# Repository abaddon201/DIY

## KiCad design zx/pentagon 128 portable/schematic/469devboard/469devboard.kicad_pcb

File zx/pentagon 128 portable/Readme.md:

# Tasks
1. build devboard for stm32f469II
2. build devboard for rom/ram
3. build devboard for Z80
3. create tap player
4. build prototype
5. create vg93 emulation
6. add AY

# Thougths
1. Use PF register for address line (placed on two neightbour sides)
2. PG0-PG7 - data pins (PI8 - slow, PI2 - absent)

2. Use PI4-11 for data line (also)

Don't use PA4, PA5 for +5V
PI8 - sow port
PC13, PC14, PC15 - slow ports (2 MHz max)

# Hardware

## Description

Cone is built from "original" Z80 CPU. Rom is extended to 128K and it's EEPROM, this can help to program it from the 
STM32 microcontroller. RAM changed to the SRAM, it's a 128K parallel RAM chip (possibly I'll extend it, but nor sure).
Music soprocessor is a AY3-8910/8912 successor: YM2149F.
All other parts would be replaced by STM32 microcontroller.
STM32 would emulate VG93 (Floppy drive), Tape playing, and create real image on the screen. It's also would
work as RAM/ROM page selector and would provide tact frequency for the CPU and AY. Also it would generate INT signal
to the CPU.

## Known issues

1.  STM32 is a 3.3V chip, but it has +5V tolerant inputs. Also all other selected chips are
TTL compatible, except Z80 CPU. Current approach to solve this: use signal converters for all input/output signals
for Z80. But it adds atleast 4 chips such that.
2. Joystick selector: I want to map different layouts to the joystic (Interface 2, QAOP_Space, Cursor, Kempston).
Possibly I can use a https://www.chipdip.ru/product/sn74ls125ad chip for that...

## Parts

STM32F469IIT6 - soldered by jlcpcb (too many small pins)
GLS29EE010-70-4C-NHE - ROM https://ru.mouser.com/ProductDetail/Greenliant/GLS29EE010-70-4C-NHE?qs=bAdOcXfFoy0toSXpScwIgg%3D%3D
IS62C1024AL-35QLI - RAM https://ru.mouser.com/ProductDetail/ISSI/IS62C1024AL-35QLI?qs=tFgq3%2FJV4HjpRgQnMjsF2Q%3D%3D
Screen - FSMC module with touchscreen http://www.lcdwiki.com/3.2inch_16BIT_Module_ILI9341_SKU:MRB3205
crystal - 8MHz https://ru.mouser.com/ProductDetail/815-ABM3B8MHZ101UT
tantalum capacitors - https://ru.mouser.com/ProductDetail/581-TPSB225K025R1200
miniUSB - https://ru.mouser.com/ProductDetail/Amphenol-FCI/10033526-N3212LF?qs=LmzVcvYPptRTPTxae6JWyQ%3D%3D
TXB0108 - level converter - https://www.ti.com/lit/ds/symlink/txb0108.pdf?HQS=TI-null-null-mousermode-df-pf-null-wwe&ts=1600075026418&ref_url=https%253A%252F%252Fru.mouser.com%252F

# Notes

## ZX Keyboard layout

https://d2j6dbq0eux0bg.cloudfront.net/images/9970794/532242200.jpg

## ZX memory layout

Memory selector port:
0x7ffd

D0-D2 - page number at 0xC000-0xFFFF
D3 - 0 - regular screen, 1 - extended (0xC000-)
D4 - 0 - 128K ROM, 1 - 48K ROM
D5 - port lock
D6-D7 - unused

Pages layouted as:

| | | | |
| 0xFFFF | | | |
| |    CPU3 | RAM0 | A14=1,A15=1 |
| 0xC000 | | | |
| 0xBFFF | | | |
| | CPU2 | RAM2 | A14=0, A15=1 |
| 0x8000 | | | |
| 0x7FFF | | | |
| | CPU1 | RAM5 | A14=1, A15=0 |
| 0x4000 | | | |
| 0x3FFF | | | |
| | CPU0 | ROM0 | A14=0, A15=0 |
| 0x0000 | | | |

http://zxbyte.ru/speccybob.htm

## INT

Freq 50Hz
Period: 20ms
Positive: 100 us
Negative: 19.9 ms

## Tape

### Sound gen

Calculation of the timer:

Arr = Fclk/(Nsamples*Fsound) - 1

### Format

Pilot tone: 807 Hz 2sec for data block, 5 sec for the header
Sync impulse: 667 tacts up, 735 tacts down
1: 1710 tacts up, down (2047 Hz)
0: 855 tacts up, down (1023 Hz)
http://zx-info.ru/?rc=12&id=5

## Screen

### Colors table

https://en.m.wikipedia.org/wiki/ZX_Spectrum_graphic_modes

## VG93

https://zx-pk.ru/threads/30269-emulyator-kontrollera-diskovoda-beta-disk-na-avr.html

## Schemes

https://zx-pk.ru/threads/940-scorpion-zs-256-turbo-(skhema).html
https://zx-pk.ru/threads/27819-pentagon-128k-opisanie-naladki.html
https://zx-pk.ru/threads/23343-novaya-plata-pentagon-128k-modifikatsiya-2014-g.html
https://m.habr.com/ru/post/498222/
http://zxdn.narod.ru/hardware.htm
http://micklab.ru/ZX%20Spectrum/Pentagon128.htm
https://www.cxemateka.ru/en/building_zx_spectrum_128k_clone_beta_disk_interface_ay_3_8910_ym2149f/all
https://zx-pk.ru/threads/27819-pentagon-128k-opisanie-naladki.html
https://zx-pk.ru/threads/23343-novaya-plata-pentagon-128k-modifikatsiya-2014-g.html
http://sblive.narod.ru/ZX-Spectrum/Pentagon128k/Pentagon128k.htm

## File formats

http://speccy.info/SCL
https://github.com/shred/tzxtools/tree/master/docs
http://www.seasip.info/ZX/unix.html

# Links

AY https://bulba.untergrund.net/elect.htm

https://documentation.help/BASin/format_tape.html
https://trolsoft.ru/ru/sch/zx-tapper
http://arduitape.blogspot.com/2016/10/introducing-tzxduino.html?m=1
https://m.habr.com/ru/post/330752/
http://zx-info.ru/?rc=12&id=5

Doing power lines right:
https://www.youtube.com/watch?v=klHu-08zyhw&list=PLiu4O2eIDAdURfQ2yeAJLD7160RrJCH3i&index=4

Ben Heck's pzx v2: https://github.com/thebenheckshow/204-tbhs-zx-kit
chips analogues: https://cxem.net/sprav/sprav48.php
zx hardware articles: https://zxpress.ru/menu/1/193
zx extended memory (128K) 
https://zxpress.ru/article.php?id=9971
http://speccy.info/%D0%9F%D0%BE%D1%80%D1%82_7FFD

pentagon timings: 
http://hype.retroscene.org/blog/773.html
https://zx-pk.ru/threads/21212-tajmingi-pentagon-128-).html?p=598258&viewfull=1#post598258

zx tr-dos: http://zxpress.ru/book_articles.php?id=1868

zx ULA verilog: 
https://github.com/fabriziotappero/ip-cores/tree/video_controller_ula_chip_for_zx_spectrum
https://opencores.org/projects/zx_ula

NedoPc:
http://nedopc.com/zxevo/zxevo.php

emulators: https://www.emu-land.net/computers/zx_spectrum/emuls/windows
zx rom disassembly: https://www.esocop.org/docs/CompleteSpectrumROMDisassemblyThe.pdf

# Datasheets

Z80 http://www.farnell.com/datasheets/91822.pdf?_ga=2.86094616.1077264973.1600187324-1828024949.1597676628
DataSheet https://ru.mouser.com/datasheet/2/176/71061-1102136.pdf
crystal https://ru.mouser.com/datasheet/2/3/abm3b-1774998.pdf
ferrite bead https://ru.mouser.com/datasheet/2/281/ENFA0003-1879738.pdf

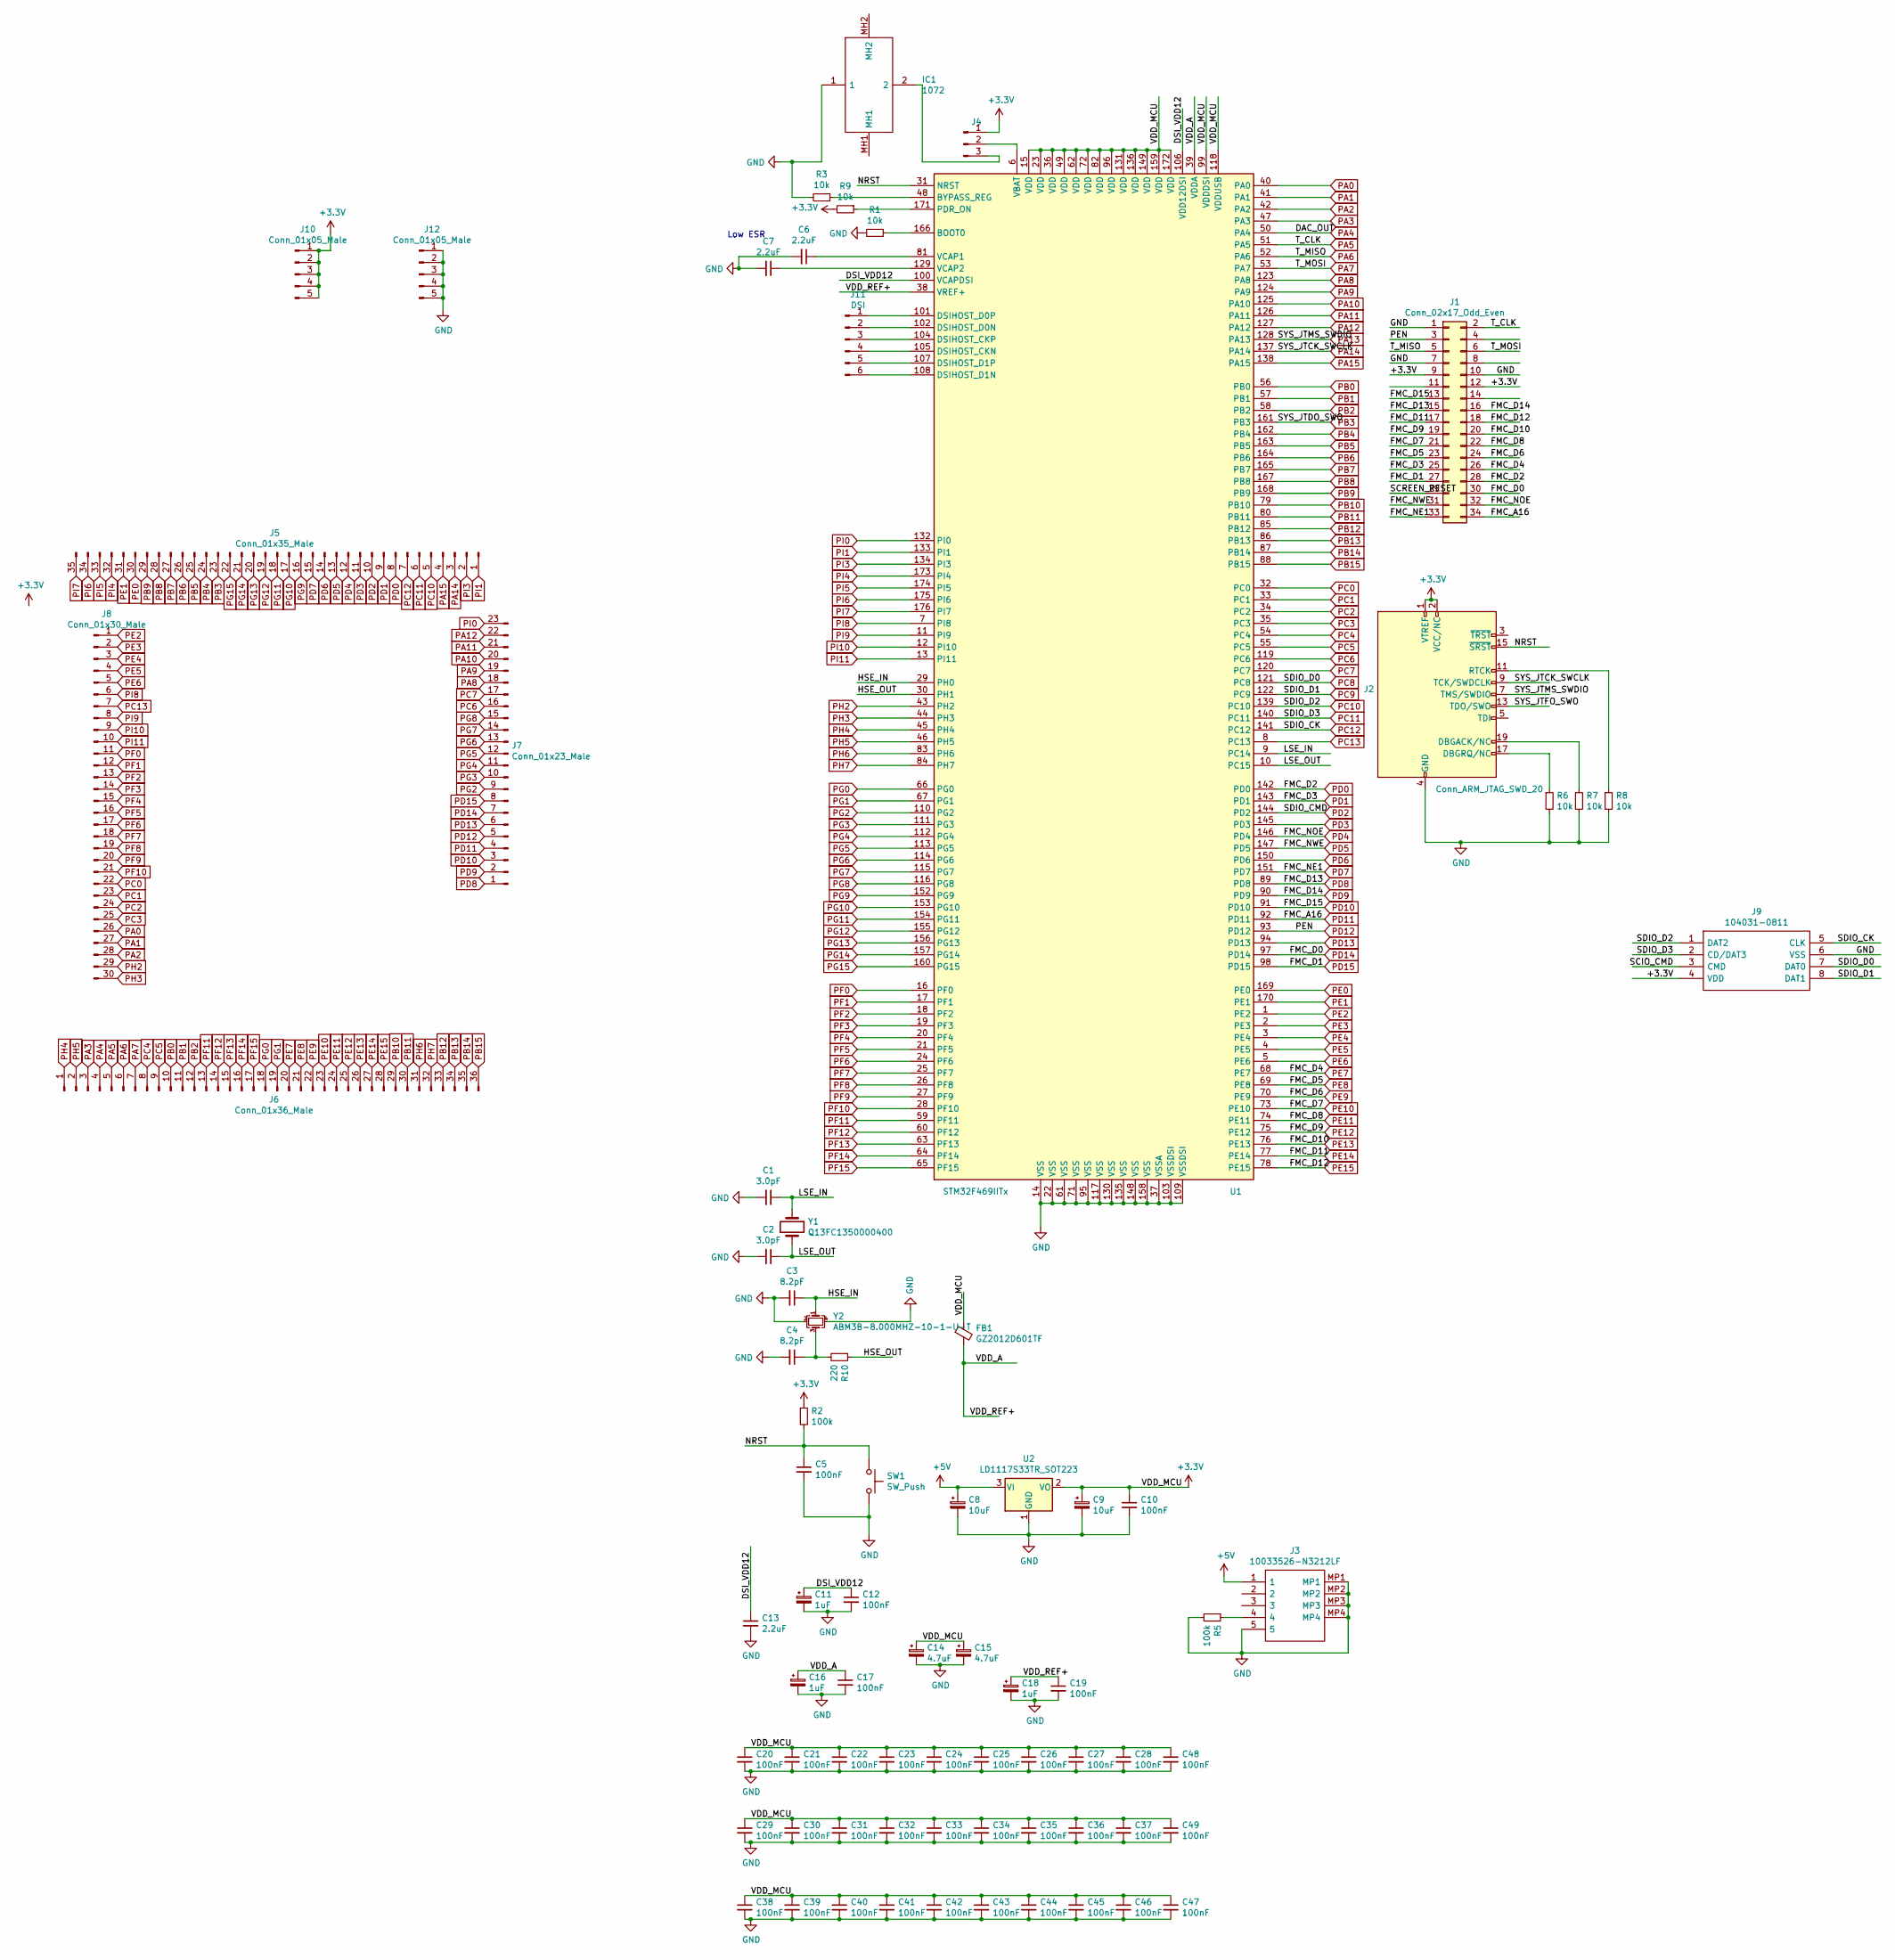
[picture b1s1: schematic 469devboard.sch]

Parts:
C1, C2: 3.0pF; C_0402_1005Metric
C3, C4: 8.2pF; C_0402_1005Metric
C5, C10, C12, C17, C19, C20, C21, C22, C23, C24, C25, C26, C27, C28, C29, C30, C31, C32, C33, C34, C35, C36, C37, C38, C39, C40, C41, C42, C43, C44, C45, C46, C47, C48, C49: 100nF; C_0402_1005Metric
C6, C7: 2.2uF; C_1210_3225Metric_Pad1.42x2.65mm_HandSolder
C8, C9: 10uF; C_0402_1005Metric
C11, C16, C18: 1uF; C_0402_1005Metric
C13: 2.2uF; C_0402_1005Metric
C14, C15: 4.7uF; C_0402_1005Metric
FB1: GZ2012D601TF; C_0805_2012Metric
IC1: 1072; Mouser Part Number 534-1072
J1: Conn_02x17_Odd_Even; PinSocket_2x17_P2.54mm_Vertical
J2: Conn_ARM_JTAG_SWD_20; PinHeader_2x10_P2.54mm_Vertical
J3: 10033526-N3212LF; 10033526N3212LF; Mouser Part Number 649-10033526-N3212LF
J4: Conn_01x03_Male; PinHeader_1x03_P2.54mm_Vertical
J5: Conn_01x35_Male; PinHeader_1x35_P2.54mm_Vertical
J6: Conn_01x36_Male; PinHeader_1x36_P2.54mm_Vertical
J7: Conn_01x23_Male; PinHeader_1x23_P2.54mm_Vertical
J8: Conn_01x30_Male; PinHeader_1x30_P2.54mm_Vertical
J9: 104031-0811; 1040310811; Mouser Part Number 538-104031-0811
J10, J12: Conn_01x05_Male; PinHeader_1x05_P2.54mm_Vertical
J11: DSI; PinHeader_1x06_P2.54mm_Vertical
R1, R3, R6, R7, R8, R9: 10k; R_0402_1005Metric
R2, R5: 100k; R_0402_1005Metric
R10: 220; R_0402_1005Metric
SW1: SW_Push; SW_DIP_SPSTx01_Slide_6.7x4.1mm_W6.73mm_P2.54mm_LowProfile_J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
U1: STM32F469IITx; LQFP-176_24x24mm_P0.5mm
U2: LD1117S33TR_SOT223; SOT-223-3_TabPin2
Y1: Q13FC1350000400; Crystal_SMD_G8-2Pin_3.2x1.5mm
Y2: ABM3B-8.000MHZ-10-1-U-T; Crystal_SMD_Abracon_ABM3B-4Pin_5.0x3.2mm

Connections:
+3V3: C9.1, C10.1, C14.1, C15.1, C20.1, C21.1, C22.1, C23.1, C24.1, C25.1, C26.1, C27.1, C28.1, C29.1, C30.1, C31.1, C32.1, C33.1, C34.1, C35.1, C36.1, C37.1, C38.1, C39.1, C40.1, C41.1, C42.1, C43.1, C44.1, C45.1, C46.1, C47.1, C48.1, C49.1, FB1.1, J2.1 (VTREF), J2.2 (VCC/NC), J4.1, J10.1, J10.2, J10.3, J10.4, J10.5, R2.1, R9.2, U1.15 (VDD), U1.23 (VDD), U1.36 (VDD), U1.49 (VDD), U1.62 (VDD), U1.72 (VDD), U1.82 (VDD), U1.96 (VDD), U1.99 (VDDDSI), U1.118 (VDDUSB), U1.131 (VDD), U1.136 (VDD), U1.149 (VDD), U1.159 (VDD), U1.172 (VDD), U2.2 (VO)
+5V: C8.1, J3.1, U2.3 (VI)
/+3.3V: J1.9, J1.12, J9.4 (VDD)
/DSI_VDD12: C11.1, C12.1, C13.1, U1.100 (VCAPDSI), U1.106 (VDD12DSI)
/HSE_IN: C3.1, U1.29 (PH0), Y2.1
/HSE_OUT: R10.1, U1.30 (PH1)
/LSE_IN: C1.1, U1.9 (PC14), Y1.1
/LSE_OUT: C2.1, U1.10 (PC15), Y1.2
/NRST: C5.1, J2.15 (~SRST~), R2.2, SW1.1, U1.31 (NRST)
/VDD_A: C16.1, C17.1, C18.1, C19.1, FB1.2, U1.38 (VREF+), U1.39 (VDDA)
GND: C1.2, C2.2, C3.2, C4.2, C5.2, C6.2, C7.2, C8.2, C9.2, C10.2, C11.2, C12.2, C13.2, C14.2, C15.2, C16.2, C17.2, C18.2, C19.2, C20.2, C21.2, C22.2, C23.2, C24.2, C25.2, C26.2, C27.2, C28.2, C29.2, C30.2, C31.2, C32.2, C33.2, C34.2, C35.2, C36.2, C37.2, C38.2, C39.2, C40.2, C41.2, C42.2, C43.2, C44.2, C45.2, C46.2, C47.2, C48.2, C49.2, IC1.1, J1.1, J1.7, J1.10, J2.4 (GND), J2.6 (GND), J2.8 (GND), J2.10 (GND), J2.12 (GND), J2.14 (GND), J2.16 (GND), J2.18 (GND), J2.20 (GND), J3.5, J3.MP1, J3.MP2, J3.MP3, J3.MP4, J9.6 (VSS), J12.1, J12.2, J12.3, J12.4, J12.5, R1.2, R3.2, R5.2, R6.2, R7.2, R8.2, SW1.2, U1.14 (VSS), U1.22 (VSS), U1.37 (VSSA), U1.61 (VSS), U1.71 (VSS), U1.95 (VSS), U1.103 (VSSDSI), U1.109 (VSSDSI), U1.117 (VSS), U1.130 (VSS), U1.135 (VSS), U1.148 (VSS), U1.158 (VSS), U2.1 (GND), Y2.2, Y2.4
unnamed: C4.1, R10.2, Y2.3
unnamed: C6.1, U1.81 (VCAP1)
unnamed: C7.1, U1.129 (VCAP2)
unnamed: IC1.2, J4.3
unnamed: J2.11 (RTCK), R8.1
unnamed: J2.17 (DBGRQ/NC), R6.1
unnamed: J2.19 (DBGACK/NC), R7.1
unnamed: J3.4, R5.1
unnamed: J4.2, U1.6 (VBAT)
unnamed: J11.1, U1.101 (DSIHOST_D0P)
unnamed: J11.2, U1.102 (DSIHOST_D0N)
unnamed: J11.3, U1.104 (DSIHOST_CKP)
unnamed: J11.4, U1.105 (DSIHOST_CKN)
unnamed: J11.5, U1.107 (DSIHOST_D1P)
unnamed: J11.6, U1.108 (DSIHOST_D1N)
unnamed: R1.1, U1.166 (BOOT0)
unnamed: R3.1, U1.48 (BYPASS_REG)
unnamed: R9.1, U1.171 (PDR_ON)
PA0: J8.26, U1.40 (PA0)
PA1: J8.27, U1.41 (PA1)
PA2: J8.28, U1.42 (PA2)
PA3: J6.3, U1.47 (PA3)
PA4: J6.4, U1.50 (PA4)
PA5: J1.2, J6.5, U1.51 (PA5)
PA6: J1.5, J6.6, U1.52 (PA6)
PA7: J1.6, J6.7, U1.53 (PA7)
PA8: J7.18, U1.123 (PA8)
PA9: J7.19, U1.124 (PA9)
PA10: J7.20, U1.125 (PA10)
PA11: J7.21, U1.126 (PA11)
PA12: J7.22, U1.127 (PA12)
PA13: J2.7 (TMS/SWDIO), U1.128 (PA13)
PA14: J2.9 (TCK/SWDCLK), J5.3, U1.137 (PA14)
PA15: J5.4, U1.138 (PA15)
PB0: J6.10, U1.56 (PB0)
PB1: J6.11, U1.57 (PB1)
PB2: J6.12, U1.58 (PB2)
PB3: J5.23, U1.161 (PB3)
PB4: J5.24, U1.162 (PB4)
PB5: J5.25, U1.163 (PB5)
PB6: J5.26, U1.164 (PB6)
PB7: J5.27, U1.165 (PB7)
PB8: J5.28, U1.167 (PB8)
PB9: J5.29, U1.168 (PB9)
PB10: J6.29, U1.79 (PB10)
PB11: J6.30, U1.80 (PB11)
PB12: J6.33, U1.85 (PB12)
PB13: J6.34, U1.86 (PB13)
PB14: J6.35, U1.87 (PB14)
PB15: J6.36, U1.88 (PB15)
PC0: J8.22, U1.32 (PC0)
PC1: J8.23, U1.33 (PC1)
PC2: J8.24, U1.34 (PC2)
PC3: J8.25, U1.35 (PC3)
PC4: J6.8, U1.54 (PC4)
PC5: J6.9, U1.55 (PC5)
PC6: J7.16, U1.119 (PC6)
PC7: J7.17, U1.120 (PC7)
PC8: J9.7 (DAT0), U1.121 (PC8)
PC9: J9.8 (DAT1), U1.122 (PC9)
PC10: J5.5, J9.1 (DAT2), U1.139 (PC10)
PC11: J5.6, J9.2 (CD/DAT3), U1.140 (PC11)
PC12: J5.7, J9.5 (CLK), U1.141 (PC12)
PC13: J8.7, U1.8 (PC13)
PD0: J1.28, J5.8, U1.142 (PD0)
PD1: J1.25, J5.9, U1.143 (PD1)
PD2: J5.10, U1.144 (PD2)
PD3: J5.11, U1.145 (PD3)
PD4: J1.32, J5.12, U1.146 (PD4)
PD5: J1.31, J5.13, U1.147 (PD5)
PD6: J5.14, U1.150 (PD6)
PD7: J1.33, J5.15, U1.151 (PD7)
PD8: J1.15, J7.1, U1.89 (PD8)
PD9: J1.16, J7.2, U1.90 (PD9)
PD10: J1.13, J7.3, U1.91 (PD10)
PD11: J1.34, J7.4, U1.92 (PD11)
PD12: J1.3, J7.5, U1.93 (PD12)
PD13: J7.6, U1.94 (PD13)
PD14: J1.30, J7.7, U1.97 (PD14)
PD15: J1.27, J7.8, U1.98 (PD15)
PE0: J5.30, U1.169 (PE0)
PE1: J5.31, U1.170 (PE1)
PE2: J8.1, U1.1 (PE2)
PE3: J8.2, U1.2 (PE3)
PE4: J8.3, U1.3 (PE4)
PE5: J8.4, U1.4 (PE5)
PE6: J8.5, U1.5 (PE6)
PE7: J1.26, J6.20, U1.68 (PE7)
PE8: J1.23, J6.21, U1.69 (PE8)
PE9: J1.24, J6.22, U1.70 (PE9)
PE10: J1.21, J6.23, U1.73 (PE10)
PE11: J1.22, J6.24, U1.74 (PE11)
PE12: J1.19, J6.25, U1.75 (PE12)
PE13: J1.20, J6.26, U1.76 (PE13)
PE14: J1.17, J6.27, U1.77 (PE14)
PE15: J1.18, J6.28, U1.78 (PE15)
PF0: J8.11, U1.16 (PF0)
PF1: J8.12, U1.17 (PF1)
PF2: J8.13, U1.18 (PF2)
PF3: J8.14, U1.19 (PF3)
PF4: J8.15, U1.20 (PF4)
PF5: J8.16, U1.21 (PF5)
PF6: J8.17, U1.24 (PF6)
PF7: J8.18, U1.25 (PF7)
PF8: J8.19, U1.26 (PF8)
PF9: J8.20, U1.27 (PF9)
PF10: J8.21, U1.28 (PF10)
PF11: J6.13, U1.59 (PF11)
PF12: J6.14, U1.60 (PF12)
PF13: J6.15, U1.63 (PF13)
PF14: J6.16, U1.64 (PF14)
PF15: J6.17, U1.65 (PF15)
PG0: J6.18, U1.66 (PG0)
PG1: J6.19, U1.67 (PG1)
PG2: J7.9, U1.110 (PG2)
PG3: J7.10, U1.111 (PG3)
PG4: J7.11, U1.112 (PG4)
PG5: J7.12, U1.113 (PG5)
PG6: J7.13, U1.114 (PG6)
PG7: J7.14, U1.115 (PG7)
PG8: J7.15, U1.116 (PG8)
PG9: J5.16, U1.152 (PG9)
PG10: J5.17, U1.153 (PG10)
PG11: J5.18, U1.154 (PG11)
PG12: J5.19, U1.155 (PG12)
PG13: J5.20, U1.156 (PG13)
PG14: J5.21, U1.157 (PG14)
PG15: J5.22, U1.160 (PG15)
PH2: J8.29, U1.43 (PH2)
PH3: J8.30, U1.44 (PH3)
PH4: J6.1, U1.45 (PH4)
PH5: J6.2, U1.46 (PH5)
PH6: J6.31, U1.83 (PH6)
PH7: J6.32, U1.84 (PH7)
PI0: J7.23, U1.132 (PI0)
PI1: J5.1, U1.133 (PI1)
PI3: J5.2, U1.134 (PI3)
PI4: J5.32, U1.173 (PI4)
PI5: J5.33, U1.174 (PI5)
PI6: J5.34, U1.175 (PI6)
PI7: J5.35, U1.176 (PI7)
PI8: J8.6, U1.7 (PI8)
PI9: J8.8, U1.11 (PI9)
PI10: J8.9, U1.12 (PI10)
PI11: J8.10, U1.13 (PI11)

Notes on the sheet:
Low ESR

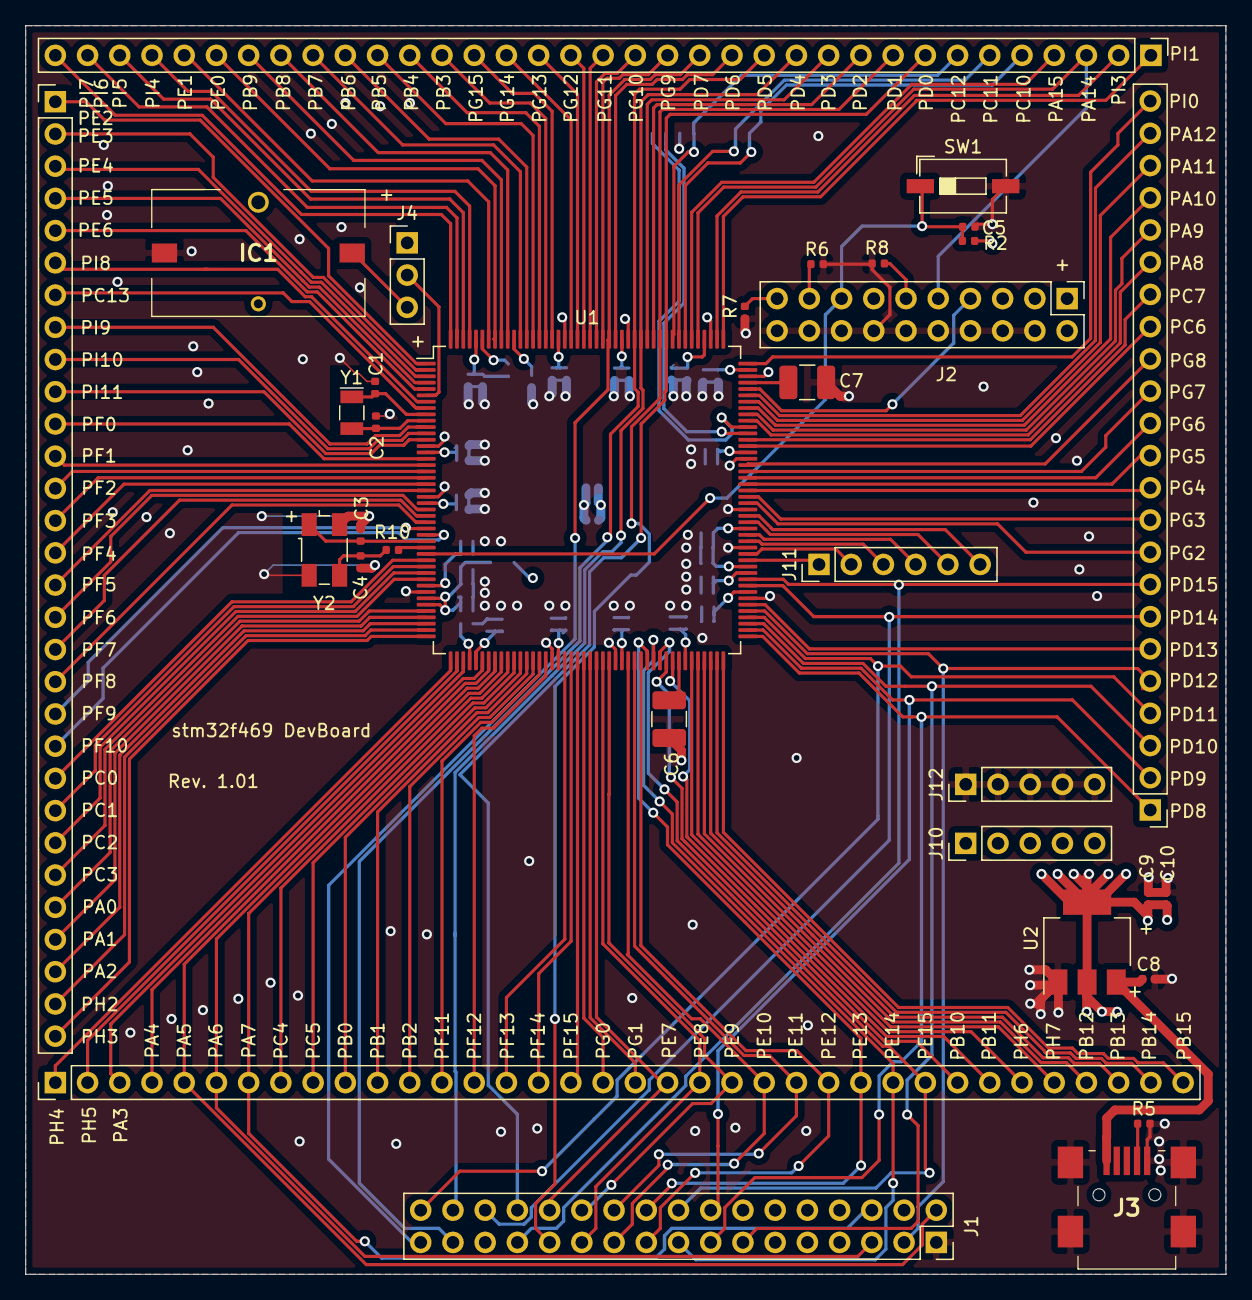
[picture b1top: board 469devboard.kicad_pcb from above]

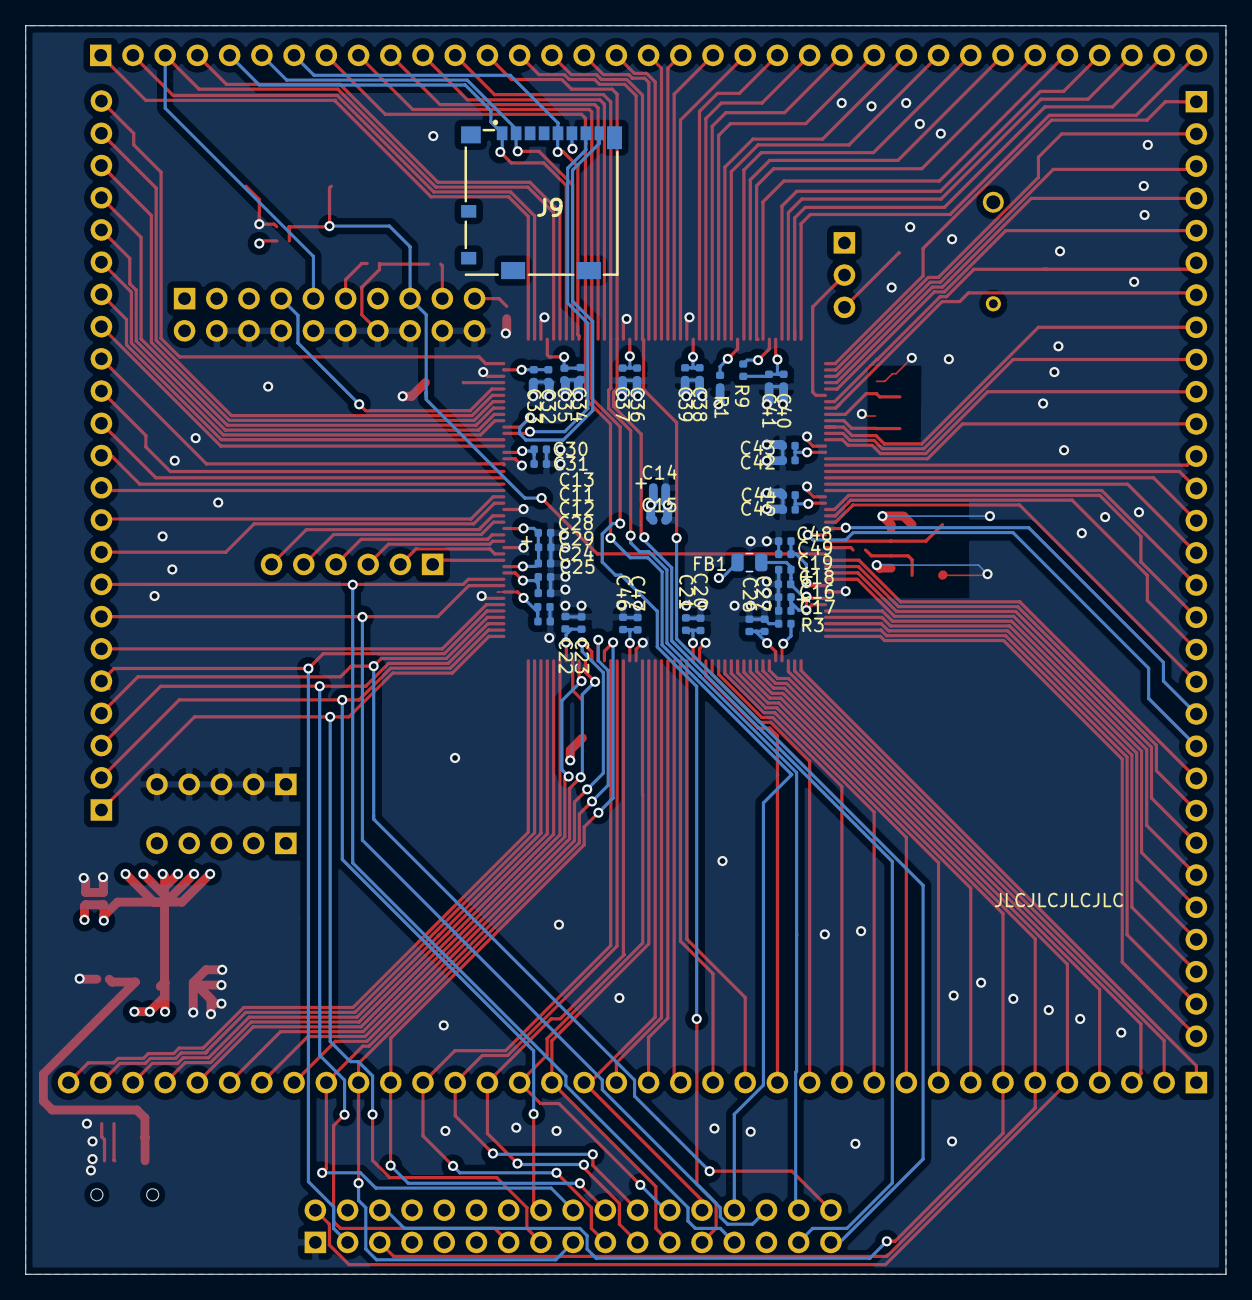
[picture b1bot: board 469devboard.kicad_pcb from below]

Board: 4 copper layers, 94.6 x 98.4 mm, 77 parts (44 on the bottom side), 156 nets.

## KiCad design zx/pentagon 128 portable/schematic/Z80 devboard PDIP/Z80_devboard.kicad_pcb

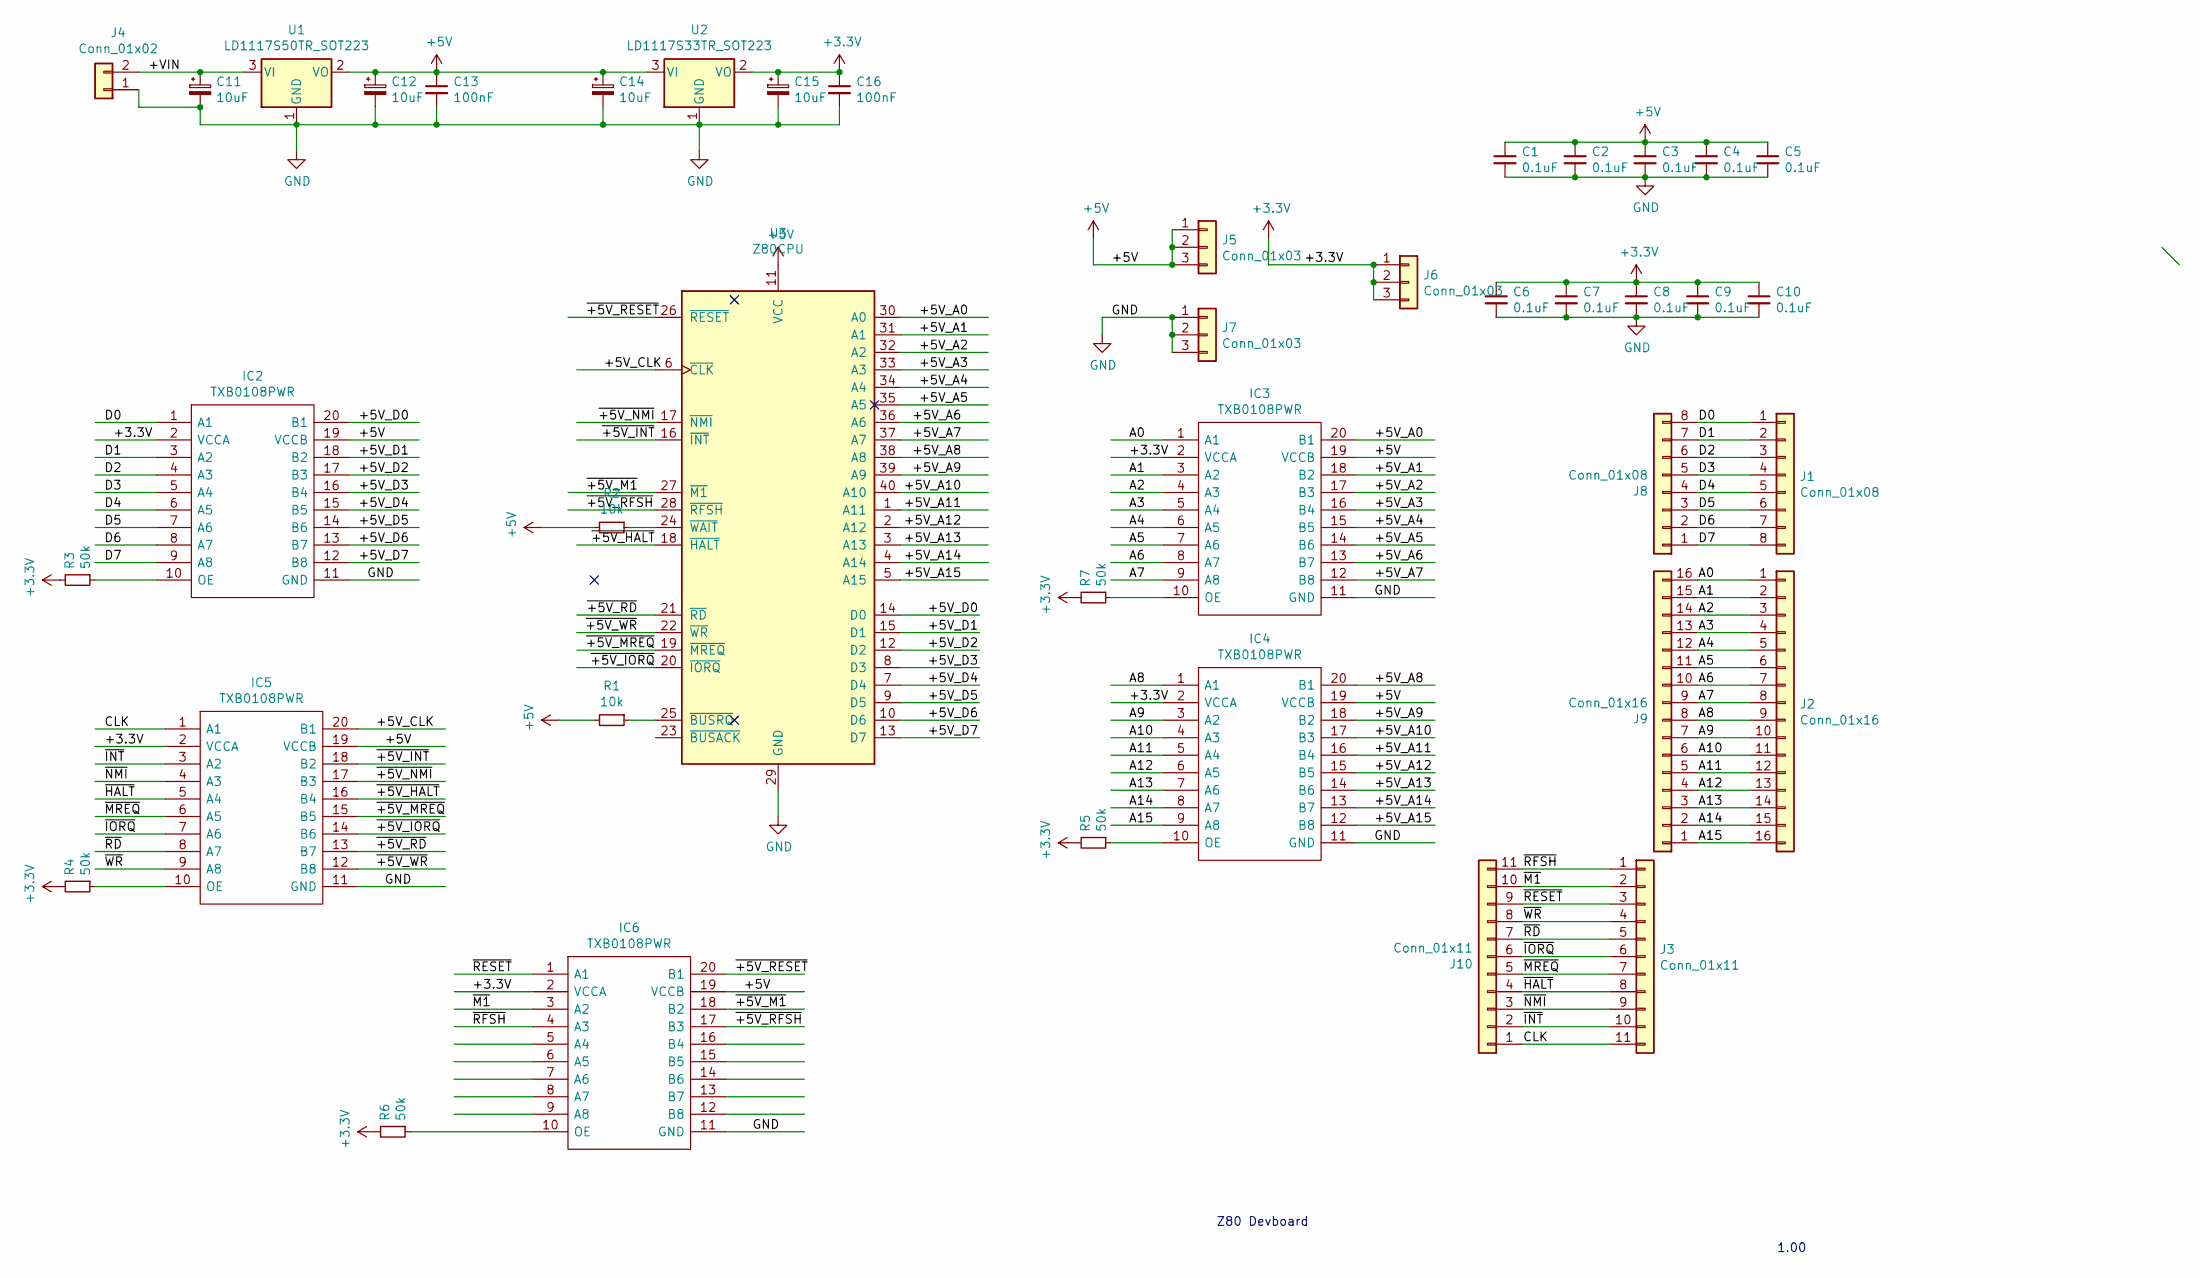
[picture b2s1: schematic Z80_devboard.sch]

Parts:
C1, C2, C3, C4, C5, C6, C7, C8, C9, C10: 0.1uF; C_0402_1005Metric
C11, C12, C14, C15: 10uF; C_0402_1005Metric
C13, C16: 100nF; C_0402_1005Metric
IC2, IC3, IC4, IC5, IC6: TXB0108PWR; SOP65P640X120-20N; Mouser Part Number 595-TXB0108PWR
J1, J8: Conn_01x08; PinHeader_1x08_P2.54mm_Vertical
J2, J9: Conn_01x16; PinHeader_1x16_P2.54mm_Vertical
J3, J10: Conn_01x11; PinHeader_1x11_P2.54mm_Vertical
J4: Conn_01x02; PinHeader_1x02_P2.54mm_Vertical
J5, J6, J7: Conn_01x03; PinHeader_1x03_P2.54mm_Vertical
R1, R2: 10k; R_0402_1005Metric
R3, R4, R5, R6, R7: 50k; R_0402_1005Metric
U1: LD1117S50TR_SOT223; SOT-223-3_TabPin2
U2: LD1117S33TR_SOT223; SOT-223-3_TabPin2
U3: Z80CPU; DIP-40_W15.24mm

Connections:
+3V3: C6.1, C7.1, C8.1, C9.1, C10.1, C15.1, C16.1, IC2.2 (VCCA), IC3.2 (VCCA), IC4.2 (VCCA), IC5.2 (VCCA), IC6.2 (VCCA), J6.1, J6.2, J6.3, R3.2, R4.2, R5.2, R6.2, R7.2, U2.2 (VO)
+5V: C1.1, C2.1, C3.1, C4.1, C5.1, C12.1, C13.1, C14.1, IC2.19 (VCCB), IC3.19 (VCCB), IC4.19 (VCCB), IC5.19 (VCCB), IC6.19 (VCCB), J5.1, J5.2, J5.3, R1.2, R2.2, U1.2 (VO), U2.3 (VI), U3.11 (VCC)
/+5V_A0: IC3.20 (B1), U3.30 (A0)
/+5V_A1: IC3.18 (B2), U3.31 (A1)
/+5V_A2: IC3.17 (B3), U3.32 (A2)
/+5V_A3: IC3.16 (B4), U3.33 (A3)
/+5V_A4: IC3.15 (B5), U3.34 (A4)
/+5V_A5: IC3.14 (B6), U3.35 (A5)
/+5V_A6: IC3.13 (B7), U3.36 (A6)
/+5V_A7: IC3.12 (B8), U3.37 (A7)
/+5V_A8: IC4.20 (B1), U3.38 (A8)
/+5V_A9: IC4.18 (B2), U3.39 (A9)
/+5V_A10: IC4.17 (B3), U3.40 (A10)
/+5V_A11: IC4.16 (B4), U3.1 (A11)
/+5V_A12: IC4.15 (B5), U3.2 (A12)
/+5V_A13: IC4.14 (B6), U3.3 (A13)
/+5V_A14: IC4.13 (B7), U3.4 (A14)
/+5V_A15: IC4.12 (B8), U3.5 (A15)
/+5V_CLK: IC5.20 (B1), U3.6 (~CLK~)
/+5V_D0: IC2.20 (B1), U3.14 (D0)
/+5V_D1: IC2.18 (B2), U3.15 (D1)
/+5V_D2: IC2.17 (B3), U3.12 (D2)
/+5V_D3: IC2.16 (B4), U3.8 (D3)
/+5V_D4: IC2.15 (B5), U3.7 (D4)
/+5V_D5: IC2.14 (B6), U3.9 (D5)
/+5V_D6: IC2.13 (B7), U3.10 (D6)
/+5V_D7: IC2.12 (B8), U3.13 (D7)
/+VIN: C11.1, J4.2, U1.3 (VI)
/A0: IC3.1 (A1), J2.1, J9.16
/A1: IC3.3 (A2), J2.2, J9.15
/A2: IC3.4 (A3), J2.3, J9.14
/A3: IC3.5 (A4), J2.4, J9.13
/A4: IC3.6 (A5), J2.5, J9.12
/A5: IC3.7 (A6), J2.6, J9.11
/A6: IC3.8 (A7), J2.7, J9.10
/A7: IC3.9 (A8), J2.8, J9.9
/A8: IC4.1 (A1), J2.9, J9.8
/A9: IC4.3 (A2), J2.10, J9.7
/A10: IC4.4 (A3), J2.11, J9.6
/A11: IC4.5 (A4), J2.12, J9.5
/A12: IC4.6 (A5), J2.13, J9.4
/A13: IC4.7 (A6), J2.14, J9.3
/A14: IC4.8 (A7), J2.15, J9.2
/A15: IC4.9 (A8), J2.16, J9.1
/CLK: IC5.1 (A1), J3.11, J10.1
/D0: IC2.1 (A1), J1.1, J8.8
/D1: IC2.3 (A2), J1.2, J8.7
/D2: IC2.4 (A3), J1.3, J8.6
/D3: IC2.5 (A4), J1.4, J8.5
/D4: IC2.6 (A5), J1.5, J8.4
/D5: IC2.7 (A6), J1.6, J8.3
/D6: IC2.8 (A7), J1.7, J8.2
/D7: IC2.9 (A8), J1.8, J8.1
/~+5V_HALT: IC5.16 (B4), U3.18 (~HALT~)
/~+5V_INT: IC5.18 (B2), U3.16 (~INT~)
/~+5V_IORQ: IC5.14 (B6), U3.20 (~IORQ~)
/~+5V_M1: IC6.18 (B2), U3.27 (~M1~)
/~+5V_MREQ: IC5.15 (B5), U3.19 (~MREQ~)
/~+5V_NMI: IC5.17 (B3), U3.17 (~NMI~)
/~+5V_RD: IC5.13 (B7), U3.21 (~RD~)
/~+5V_RESET: IC6.20 (B1), U3.26 (~RESET~)
/~+5V_RFSH: IC6.17 (B3), U3.28 (~RFSH~)
/~+5V_WR: IC5.12 (B8), U3.22 (~WR~)
/~HALT: IC5.5 (A4), J3.8, J10.4
/~INT: IC5.3 (A2), J3.10, J10.2
/~IORQ: IC5.7 (A6), J3.6, J10.6
/~M1: IC6.3 (A2), J3.2, J10.10
/~MREQ: IC5.6 (A5), J3.7, J10.5
/~NMI: IC5.4 (A3), J3.9, J10.3
/~RD: IC5.8 (A7), J3.5, J10.7
/~RESET: IC6.1 (A1), J3.3, J10.9
/~RFSH: IC6.4 (A3), J3.1, J10.11
/~WR: IC5.9 (A8), J3.4, J10.8
GND: C1.2, C2.2, C3.2, C4.2, C5.2, C6.2, C7.2, C8.2, C9.2, C10.2, C11.2, C12.2, C13.2, C14.2, C15.2, C16.2, IC2.11 (GND), IC3.11 (GND), IC4.11 (GND), IC5.11 (GND), IC6.11 (GND), J4.1, J7.1, J7.2, J7.3, U1.1 (GND), U2.1 (GND), U3.29 (GND)
unnamed: IC2.10 (OE), R3.1
unnamed: IC3.10 (OE), R7.1
unnamed: IC4.10 (OE), R5.1
unnamed: IC5.10 (OE), R4.1
unnamed: IC6.10 (OE), R6.1
unnamed: R1.1, U3.25 (~BUSRQ~)
unnamed: R2.1, U3.24 (~WAIT~)

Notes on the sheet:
1.00
Z80 Devboard

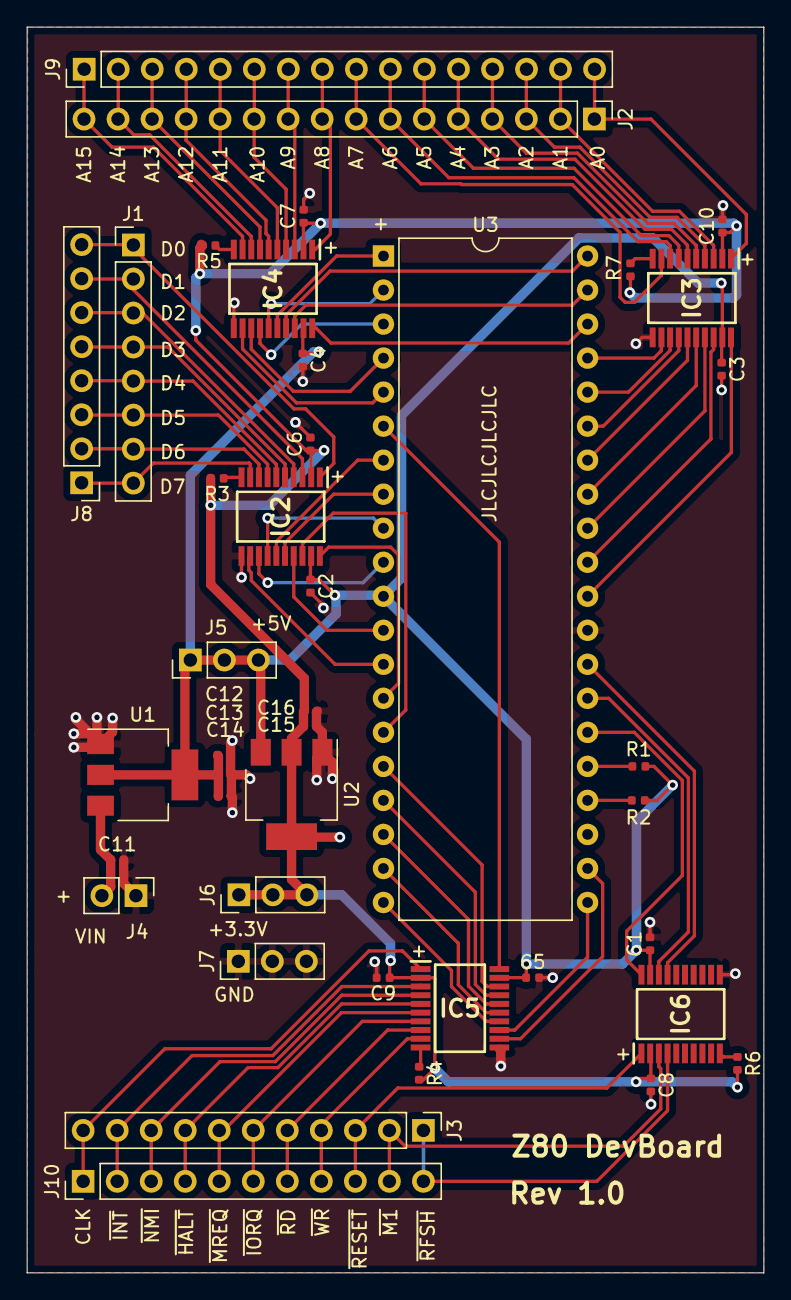
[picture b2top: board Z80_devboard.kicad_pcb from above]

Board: 2 copper layers, 55.0 x 93.0 mm, 41 parts (0 on the bottom side), 81 nets.
